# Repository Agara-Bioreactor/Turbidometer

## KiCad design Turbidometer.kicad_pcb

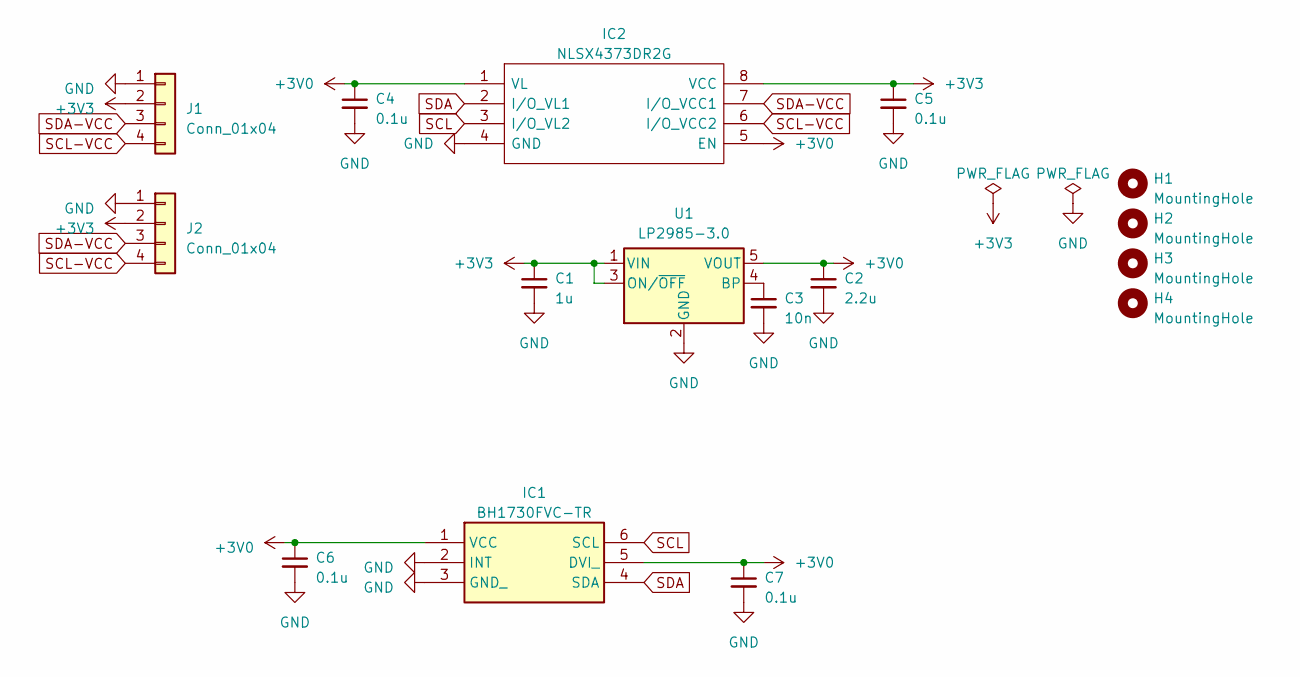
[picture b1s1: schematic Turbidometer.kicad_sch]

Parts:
C1: 1u; C_0805_2012Metric_Pad1.18x1.45mm_HandSolder
C2: 2.2u; C_0805_2012Metric_Pad1.18x1.45mm_HandSolder
C3: 10n; C_0805_2012Metric_Pad1.18x1.45mm_HandSolder
C4, C5, C6, C7: 0.1u; C_0805_2012Metric_Pad1.18x1.45mm_HandSolder
H1, H2, H3, H4: MountingHole; MountingHole_3.2mm_M3_ISO14580_Pad
IC1: BH1730FVC-TR; BH1730FVCTR; Manufacturer_Part_Number BH1730FVC-TR; Mouser Part Number 755-BH1730FVC-TR
IC2: NLSX4373DR2G; SOIC-8_3.9x4.9mm_P1.27mm; Manufacturer_Part_Number NLSX4373DR2G; Mouser Part Number 863-NLSX4373DR2G
J1: Conn_01x04; JST_SH_SM04B-SRSS-TB_1x04-1MP_P1.00mm_Horizontal
J2: Conn_01x04; JST_XH_B4B-XH-AM_1x04_P2.50mm_Vertical
U1: LP2985-3.0; SOT-23-5

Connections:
+3V0: C2.1, C4.1, C6.1, C7.1, IC1.1 (VCC), IC1.5 (DVI_), IC2.1 (VL), IC2.5 (EN), U1.5 (VOUT)
+3V3: C1.1, C5.1, IC2.8 (VCC), J1.2, J2.2, U1.1 (VIN), U1.3 (ON/~OFF)
GND: C1.2, C2.2, C3.2, C4.2, C5.2, C6.2, C7.2, IC1.2 (INT), IC1.3 (GND_), IC2.4 (GND), J1.1, J2.1, U1.2 (GND)
unnamed: C3.1, U1.4 (BP)
SCL: IC1.6 (SCL), IC2.3 (I/O_VL2)
SCL-VCC: IC2.6 (I/O_VCC2), J1.4, J2.4
SDA: IC1.4 (SDA), IC2.2 (I/O_VL1)
SDA-VCC: IC2.7 (I/O_VCC1), J1.3, J2.3

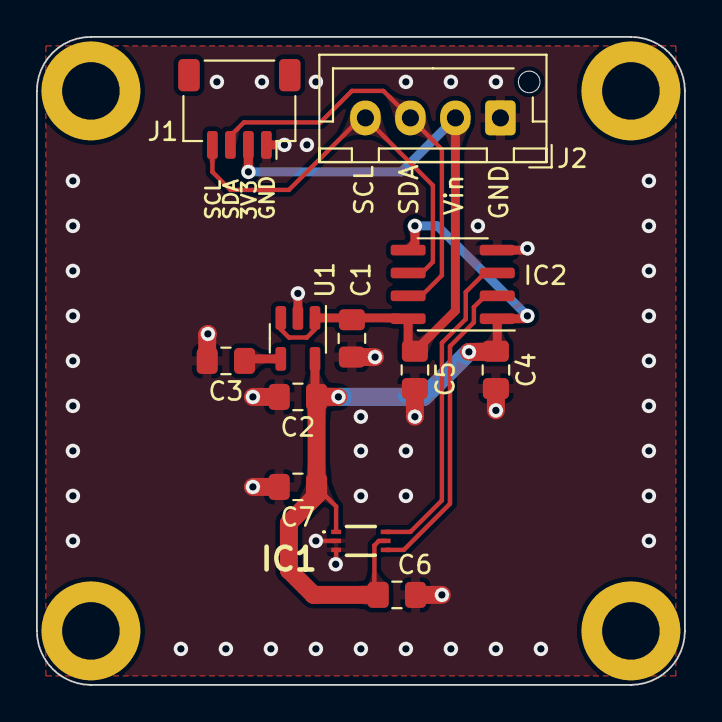
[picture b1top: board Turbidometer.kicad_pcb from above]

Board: 2 copper layers, 36.0 x 36.0 mm, 16 parts (0 on the bottom side), 8 nets.

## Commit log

2023-04-01 Adding initial revision of turbidometer PCB
2023-04-02 Added missing tracks and several changes to satisfy ERC
2023-04-02 generated manufacturing outputs for cost check
2023-04-02 Adding useful silk
2023-04-08 adding teardrops, fixing silk
